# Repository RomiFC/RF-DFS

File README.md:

# :satellite: Radio Frequency Direction Finding System

The RF-DFS is a movable 3-meter dish antenna with azimuth and elevation drivers to locate the source of RF interference. This project combines the function of the DFS with the RF - Environmental Monitoring System; a similar utility that is built off of an effectively isotropic antenna. Both RF chains are connected to a Keysight N9040B Spectrum Analyzer and are controlled by a Python GUI.

**Hardware:** Automation Direct P1AM-100 PLC with 15-point discrete output module, Parker Hannifin ACR9000 Motion Controller, 2 Aries AR-04AE Servo Drives, Keysight N9040B Spectrum Analyzer, and a Windows computer.

## 🏗️ Tech Stack

```mermaid
graph BT

    subgraph Hardware
    P1AM
    win[Windows Machine]
    ACR9000
    AR-04AE
    N9040B
    end

    subgraph Firmware
    C++
    AcroBASIC
    SCPI
    end

    subgraph client[Edge Client]
    Python([Python Front End])
    end

    subgraph Back End
    Database[(PostgreSQL<br>Database)]
    Server([Python Server])
    end

    C++ -->|Serial| Python
    AcroBASIC -->|Serial| Python
    SCPI -->|GPIB/LAN| Python

    P1AM --> C++
    win --> Python
    ACR9000 & AR-04AE --> AcroBASIC
    N9040B --> SCPI
    client --> Database
    Database <--> Server
```

## 🚀 Deployment Requirements

- [NI-VISA](https://www.ni.com/en/support/downloads/drivers/download.ni-visa.html) or other suitable PyVISA backend.
- Ethernet, GPIB, serial, or other SCPI instrument connection.
  - [NI-488.2](https://www.ni.com/en/support/downloads/drivers/download.ni-488-2.html#484357) if using GPIB.

## 🛠️ Development Requirements

- All above requirements.
- [Python 3.11+](https://www.python.org/) and an understanding of the following:
  - [tkinter](https://docs.python.org/3/library/tkinter.html#module-tkinter)
  - [pySerial](https://pypi.org/project/pyserial/)
  - [PyVisa](https://pyvisa.readthedocs.io/en/latest/)
  - [matplotlib](https://matplotlib.org/)
- Suitable Python IDE (Recommended [VSCode](https://code.visualstudio.com/))
- Python packager (Recommended [PyInstaller](https://pyinstaller.org/en/stable/))
- [PlatformIO](https://platformio.org/) for updating PLC firmware.

> [!NOTE]
> Freezing tools (Such as PyInstaller) package the entire Python Interpreter and installed libraries which generates large executables and could be flagged as a virus. It is recommended to create a virtual environment and only install/package the libraries used in the program. These executables will also only work on the OS that built them (A Windows deployment must be built on a Windows computer).

### Packages

```bash
pip install pyserial
```

```bash
pip install pyvisa
```

```bash
pip install matplotlib
```

```bash
pip install numpy
```

```bash
pip install apscheduler
```

```bash
pip install ttkthemes
```

```bash
pip install tkcalendar
```

```bash
pip install tktimepicker
```

## :mailbox: Authors

- [Remy Nguyen](https://github.com/RomiFC)
- [Hina Suzuki](https://github.com/hina18201716)

<picture>
  <source media="(prefers-color-scheme: dark)" srcset="https://public.nrao.edu/wp-content/uploads/2023/02/logoGroupWhite.png">
  <source media="(prefers-color-scheme: light)" srcset="https://public.nrao.edu/wp-content/uploads/2023/02/logoGroupColor.png">
  
</picture>

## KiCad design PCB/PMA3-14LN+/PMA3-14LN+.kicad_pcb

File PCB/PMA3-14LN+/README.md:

# Changelog

## Revision B - 10/24/2023

### Added

- More PTH vias around and directly under RF components.
- Another layer of via picketing around transmission line.
- Silkscreen revision indicator.
- Dimensioning to assembly drawing.

### Changed

- Removed Hammond 1554B compatibility due to difficulties in assembly and weatherproofing SMA connectors. Overall board is smaller at 35mm x 35mm.
- SMA Connectors replaced with Mueller BU-1420761881 which have an upper frequency of 26.5 GHz and better impedance matching at the landing.
- GCPW dimensions from w = 0.415mm, s = 0.6mm, to w = 0.37mm, s = 0.2mm and added 0.375mm taper from SMA clearance to GCPW clearance.

### Fixed

- C9 footprint now correctly matches schematic (0402 --> 1206).
- Moved SMA footprints closer to board edge to reduce filing prior to assembly.

## Revision A - 4/12/2023

### First revision 🎉🎉🎉

- Board is built to 4-layer OSHPark specifications
- This amplifier showed slightly lower gain than expected, rolling off quicker with frequency. This is likely due to the SMA connector landings which had a known impedance mismatch, resulting in a steep rolloff somewhere between 12 and 18 GHz.

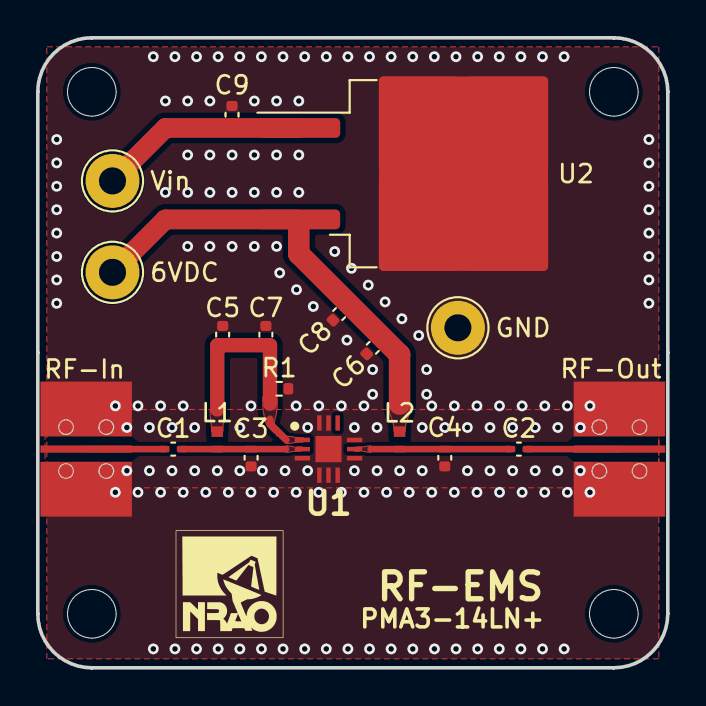
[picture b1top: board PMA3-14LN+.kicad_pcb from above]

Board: 4 copper layers, 35.0 x 35.0 mm, 20 parts (0 on the bottom side), 8 nets.

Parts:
6VDC: 6VDC; TestPoint_Loop_D2.54mm_Drill1.5mm_Beaded
 : FabDrawing-4Layer-Metric-Compact-OSH
C1, C2: 0.01 uF; C_0402_1005Metric
C3: 0.2 pF; C_0402_1005Metric
C4: 0.1 pF; C_0402_1005Metric
C5, C6: 100 pF; C_0402_1005Metric
C7: 0.1 uF; C_0402_1005Metric
C8: 0.1 uf; C_0402_1005Metric
C9: 0.33 uF; C_0402_1005Metric
GND: GND; TestPoint_Loop_D2.54mm_Drill1.5mm_Beaded
L1, L2: 900 nH; L_0402_1005Metric
R1: 510 Ω; R_0402_1005Metric
RF-In: Conn_Coaxial; Mueller BU-1420761881-RevB
RF-Out: Conn_Coaxial; Mueller BU-1420761881-RevB
U1: PMA3-14LN+; QFN51P300X300X89-13N
U2: L7806; TO-263-2
Vin: Vin; TestPoint_Loop_D2.54mm_Drill1.5mm_Beaded

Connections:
6VDC: 6VDC.1, C6.1, C8.1, L2.1, U2.3 (OUT)
GND: C3.1, C4.1, C5.1, C6.2, C7.1, C8.2, C9.2, GND.1, R1.2, RF-In.2 (Ext), RF-Out.2 (Ext), U1.3 (NC_1), U1.4 (NC_2), U1.5 (NC_3), U1.6 (NC_4), U1.7 (NC_5), U1.9 (NC_6), U1.11 (NC_8), U1.12 (NC_9), U1.13 (GND), U2.2 (GND)
unnamed: C5.2, C7.2, L1.1, R1.1, U1.1 (CURRENT_MIRROR)
unnamed: C1.2, C3.2, L1.2, U1.2 (RF-IN)
unnamed: C2.1, C4.2, L2.2, U1.8 (RF-OUT_&_VDD)
unnamed: C1.1, RF-In.1 (In)
unnamed: C2.2, RF-Out.1 (In)
Vin: C9.1, U2.1 (IN), Vin.1

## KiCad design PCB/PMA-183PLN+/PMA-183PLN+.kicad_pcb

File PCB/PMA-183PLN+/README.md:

# Changelog

## Revision B - 7/5/2023

### Added

- More PTH vias around and directly under RF components.
- Another layer of via picketing around transmission line.
- Silkscreen revision indicator.
- Dimensioning to assembly drawing.

### Changed

- Removed Hammond 1554B compatibility due to difficulties in assembly and weatherproofing SMA connectors.
- GCPW dimensions from w = 0.41mm, s = 0.2mm, to w = 0.37mm, s = 0.2mm and added 0.375mm taper from SMA clearance to GCPW clearance.

### Fixed

- C9 footprint now correctly matches schematic (0402 --> 1206).
- Moved SMA footprints closer to board edge to reduce filing prior to assembly.

## Revision A - 6/12/2023

### First revision 🎉🎉🎉

- Board is built to 4-layer OSHPark specifications
- Testing shows amplifier oscillates strongly at ~18.5 GHz. This occurs both when the amplifier is biased through the regulator or directly from a DC power supply. SMA landings were also copied from test coupons so that can likely be ruled out. This is possibly due to the lack of PTH vias directly under the IC or the tuning/spacing of picketing around the transmission line.

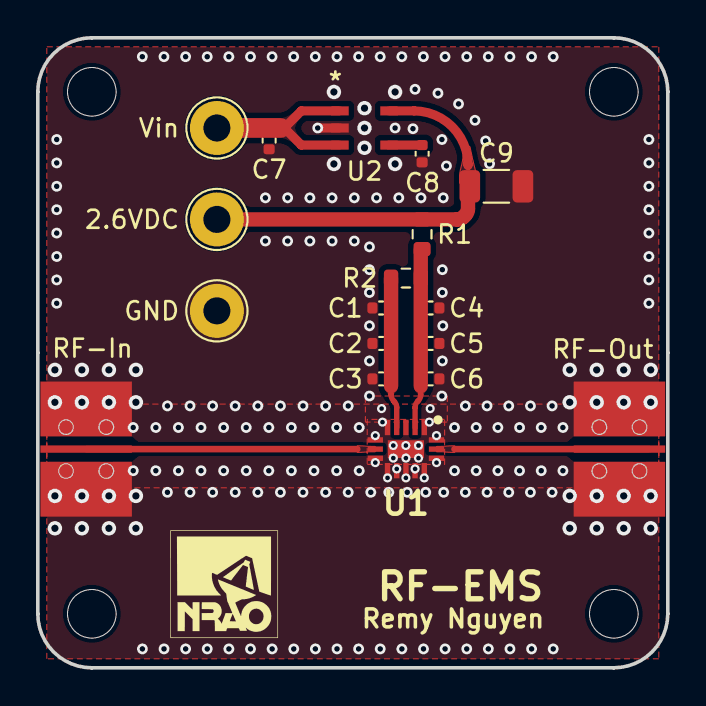
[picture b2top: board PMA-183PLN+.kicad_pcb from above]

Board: 4 copper layers, 35.0 x 35.0 mm, 20 parts (0 on the bottom side), 8 nets.

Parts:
2.6VDC: 2.6VDC; TestPoint_Loop_D2.54mm_Drill1.5mm_Beaded
 : FabDrawing-4Layer-Metric-Compact-OSH
 #2: LOGO; GCPW_osh3_90mm_user
C1, C4, C7: 0.33 uF; C_0402_1005Metric
C2, C5: 1000 pF; C_0402_1005Metric
C3, C6: 100 pF; C_0402_1005Metric
C8: 470 pF; C_0402_1005Metric
C9: 2.2 uF; C_1206_3216Metric
GND: GND; TestPoint_Loop_D2.54mm_Drill1.5mm_Beaded
R1: 10 Ω; R_0603_1608Metric
R2: 180 Ω; R_0603_1608Metric
RF-In: Conn_Coaxial; Mueller BU-1420761881
RF-Out: Conn_Coaxial; Mueller BU-1420761881
U1: PMA-183PLN+; QFN51P250X350X85-17N
U2: MIC5219-2.6YM5-TR; SOT-23-5_M5_MCH
Vin: Vin; TestPoint_Loop_D2.54mm_Drill1.5mm_Beaded

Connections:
2.6VDC: 2.6VDC.1, C9.1, R1.2, U2.5 (OUT)
GND: C1.1, C2.1, C3.1, C4.2, C5.2, C6.2, C7.2, C8.2, C9.2, GND.1, RF-In.2 (Ext), RF-Out.2 (Ext), U1.1 (NC_1), U1.3 (NC_2), U1.5 (NC_3), U1.6 (GND_1), U1.8 (GND_2), U1.9 (NC_4), U1.10 (NC_5), U1.11 (NC_6), U1.12 (NC_7), U1.13 (NC_8), U1.14 (GND_3), U1.16 (GND_4), U1.17 (EP), U2.2 (GND)
unnamed: RF-In.1 (In), U1.7 (RF-IN)
unnamed: RF-Out.1 (In), U1.15 (RF-OUT)
unnamed: C4.1, C5.1, C6.1, R1.1, R2.2, U1.2 (VDD)
unnamed: C1.2, C2.2, C3.2, R2.1, U1.4 (VE)
unnamed: C8.1, U2.4 (BYP)
Vin: C7.1, U2.1 (IN), U2.3 (EN), Vin.1

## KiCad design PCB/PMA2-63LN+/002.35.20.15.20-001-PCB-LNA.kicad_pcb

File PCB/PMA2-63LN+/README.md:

# Changelog

## Revision C - 2/23/2024

### Added

- SMA connectors dimensioned.

### Changed

- Drawing sheets changed from A4 to Letter size.
- New stackup table format.

### Fixed

- SMA launch pad widened with ground plane cutout to improve Z-matching.
- Mounting holes now correctly part of GND net.

## Revision B - 1/23/2024

### Added

- GCPW cross-section to assembly drawing.
- Board characteristics to assembly drawing.
- Board dimensioning to assembly drawing.
- Test points for DC power as an alternative to SMA.
- Test points for Iadj control.
- More PTH vias around and directly under RF components.
- Layer indicator to top left of assembly drawing.

### Changed

- Stackup changed from 2-layer, 30 mil RO4350b to 4-layer OSHPark specifications.
- Board compacted in attempt to reduce oscillations from quarter-wave resonance.
- Connector references changed from J- to more descriptive names.

### Fixed

- Removed back mask from linear regulator pads to improve thermal conductance.
- Iadj resistor to ground replaced with voltage divider for control from +5VDC to GND.

## Revision A - 7/6/2023

### First revision 🎉🎉🎉

- Board is built on 30-mil Rogers RO4350b with 2 layers. Contains two LNAs with their own linear regulators and a 1 dB attenuator between them to improve return loss.
- Testing shows amplifier instability/oscillations at ~10.8 GHz with both PMA2-63LN+ and PMA2-123LN+. This was caused by shunt capacitance introduced from the relatively large SMA landing pads and Molex center conductor.
- 30-mil substrate proved to be thin and more prone to breakage/flexing, especially when torquing SMA connectors.

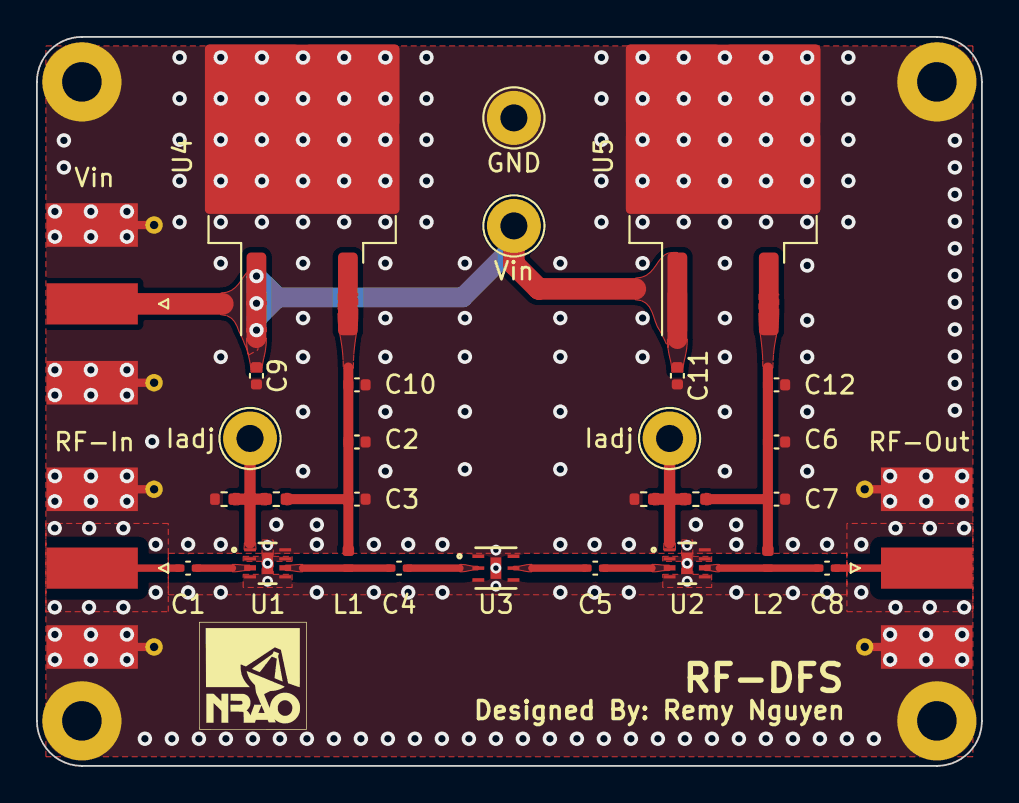
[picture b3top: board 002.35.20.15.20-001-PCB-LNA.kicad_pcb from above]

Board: 4 copper layers, 52.5 x 40.5 mm, 30 parts (0 on the bottom side), 14 nets.

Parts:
C1, C4, C5, C8: 150pF; C_0402_1005Metric
C2, C6: 1uF; C_0402_1005Metric
C3, C7: 100pF; C_0402_1005Metric
C9, C11: 0.33uF; C_0402_1005Metric
C10, C12: 0.1uF; C_0402_1005Metric
GND: GND; TestPoint_Loop_D2.54mm_Drill1.5mm_Beaded
Iadj: TestPoint; TestPoint_Loop_D2.54mm_Drill1.5mm_Beaded
Iadj#2: TestPoint; TestPoint_Loop_D2.54mm_Drill1.5mm_Beaded
L1, L2: 56nH; L_0402_1005Metric
R1, R2, R3, R4: 100k; R_0402_1005Metric
RF-In: Conn_Coaxial; SMA_Molex_73251-1153_EdgeMount_Horizontal
RF-Out: Conn_Coaxial; SMA_Molex_73251-1153_EdgeMount_Horizontal
U1, U2: PMA2-63LN+; SON8_PMA2_MNC
U3: YAT-1A+; MC1630_MNC
U4, U5: L7805; TO-263-2
Vin: Vin; TestPoint_Loop_D2.54mm_Drill1.5mm_Beaded
Vin#2: Conn_Coaxial; SMA_Molex_73251-1153_EdgeMount_Horizontal

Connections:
/LNA Biasing1/LNA-IN: C1.1, RF-In.1 (In)
/LNA Biasing1/LNA-OUT: C4.2, U3.2 (RF-IN)
/LNA Biasing2/LNA-IN: C5.1, U3.5 (RF-OUT)
/LNA Biasing2/LNA-OUT: C8.2, RF-Out.1 (In)
GND: C2.2, C3.2, C6.2, C7.2, C9.2, C10.2, C11.2, C12.2, GND.1, R1.1, R2.1, RF-In.2 (Ext), RF-Out.2 (Ext), U1.2 (GND), U1.4 (GND), U1.5 (GND), U1.7 (GND), U1.8 (GND), U1.9 (EPAD), U2.2 (GND), U2.4 (GND), U2.5 (GND), U2.7 (GND), U2.8 (GND), U2.9 (EPAD), U3.1 (GND), U3.3 (GND), U3.4 (GND), U3.6 (GND), U3.7 (GND), U4.2 (GND), U5.2 (GND), Vin#2.2 (Ext)
unnamed: Iadj#2.1, R1.2, R3.1, U1.1 (LADJ)
unnamed: C1.2, U1.3 (RF-IN)
unnamed: C4.1, L1.2, U1.6 (RF-OUT)
unnamed: Iadj.1, R2.2, R4.1, U2.1 (LADJ)
unnamed: C5.2, U2.3 (RF-IN)
unnamed: C8.1, L2.2, U2.6 (RF-OUT)
Vdd1: C2.1, C3.1, C10.1, L1.1, R3.2, U4.3 (OUT)
Vdd2: C6.1, C7.1, C12.1, L2.1, R4.2, U5.3 (OUT)
Vin: C9.1, C11.1, U4.1 (IN), U5.1 (IN), Vin.1, Vin#2.1 (In)

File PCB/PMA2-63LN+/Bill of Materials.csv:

"#","Reference","Qty","Value","Footprint","DNP"
"1","C1, C4, C5, C8","4","150pF","Capacitor_SMD:C_0402_1005Metric",""
"2","C2, C6","2","1uF","Capacitor_SMD:C_0402_1005Metric",""
"3","C3, C7","2","100pF","Capacitor_SMD:C_0402_1005Metric",""
"4","C9, C11","2","0.33uF","Capacitor_SMD:C_0402_1005Metric",""
"5","C10, C12","2","0.1uF","Capacitor_SMD:C_0402_1005Metric",""
"6","J1, J2, J3","3","Conn_Coaxial","Connector_Coaxial:SMA_Molex_73251-1153_EdgeMount_Horizontal",""
"7","L1, L2","2","56nH","Inductor_SMD:L_0402_1005Metric",""
"8","R1, R2","2","100k","Resistor_SMD:R_0402_1005Metric",""
"9","U1, U2","2","PMA2-63LN+","Imports:SON8_PMA2_MNC",""
"10","U3","1","YAT-1A+","Imports:MC1630_MNC",""
"11","U4, U5","2","L7805","Package_TO_SOT_SMD:TO-263-2",""

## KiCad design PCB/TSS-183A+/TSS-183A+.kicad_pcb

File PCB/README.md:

# Board Files

Any footprints, symbols, and models, not included with KiCad 7.0/8.0 should be added the libraries in [_dependencies](./_dependencies). Ensure that all projects are in their own directory and that each project is linked to the following library paths:

### Footprints

```pcbnew
${KIPRJMOD}/../_dependencies/footprints
```

### Symbols

```pcbnew
${KIPRJMOD}/../_dependencies/symbols/rf-dfs.kicad_sym
```

### 3D Models

Footprints should be linked to imported 3D models using the following path:

```pcbnew
${KIPRJMOD}/../_dependencies/3dmodels/<FILE_NAME>.STEP
```

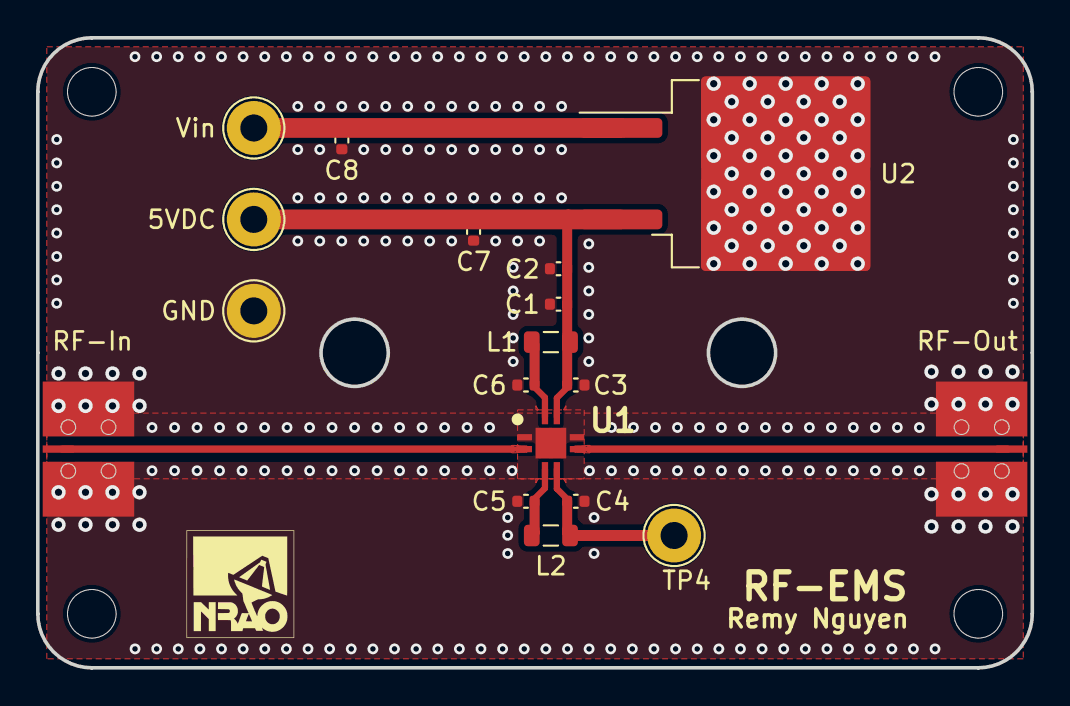
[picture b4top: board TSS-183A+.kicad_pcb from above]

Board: 4 copper layers, 55.3 x 35.0 mm, 20 parts (0 on the bottom side), 8 nets.

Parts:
5VDC: 5VDC; TestPoint_Loop_D2.54mm_Drill1.5mm_Beaded
 : LOGO; GCPW_osh2_90mm_user
 #2: FabDrawing-4Layer-Metric-Compact-OSH
C1: 5.6 pF; C_0402_1005Metric
C2: 18 pF; C_0402_1005Metric
C3, C4, C5: 1 nF; C_0402_1005Metric
C6, C7: 0.1 uF; C_0402_1005Metric
C8: 0.33 uF; C_0402_1005Metric
GND: GND; TestPoint_Loop_D2.54mm_Drill1.5mm_Beaded
L1, L2: 3.3 nH; L_0805_2012Metric
RF-In: Conn_Coaxial; Mueller BU-1420761881
RF-Out: Conn_Coaxial; Mueller BU-1420761881
TP4: Vg; TestPoint_Loop_D2.54mm_Drill1.5mm_Beaded
U1: TSS-183A+; QFN66P300X300X89-9N
U2: L7805; TO-263-2
Vin: Vin; TestPoint_Loop_D2.54mm_Drill1.5mm_Beaded

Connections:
5VDC: 5VDC.1, C1.1, C2.1, C3.1, C7.1, L1.1, U1.7 (VDD2), U2.3 (OUT)
GND: C1.2, C2.2, C3.2, C4.1, C5.2, C6.1, C7.2, C8.2, GND.1, RF-In.2 (Ext), RF-Out.2 (Ext), U1.1 (NC_1), U1.6 (NC_2), U1.9 (EP), U2.2 (GND)
unnamed: RF-In.1 (In), U1.2 (RF-IN)
unnamed: RF-Out.1 (In), U1.5 (RF-OUT)
unnamed: C6.2, L1.2, U1.8 (VDD1)
unnamed: C5.1, L2.1, U1.3 (VG1)
unnamed: C4.2, L2.2, TP4.1, U1.4 (VG2)
Vin: C8.1, U2.1 (IN), Vin.1

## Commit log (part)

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2024-07-05 Updated RF block diagram
2024-07-09 Fixed PMA2-63LN+ changelog dates
2024-08-06 PLC code added with basic functionality
    - Successfully receives and parses strings from serial into opcodes.
    - Needs additional functionality/opcodes for configuration and error messaging
2024-08-07 Moved opcodes to opcodes.h and added doxygen comments (PLC)
2024-08-07 Changed opcode syntax for sleep operations (PLC)
2024-08-07 Added more opcode functionality to plc
2024-08-09 Fixed bug where scpiApplyConfig called ttk::spinbox get() twice
2024-08-09 Limited GUI root window size to initial value
2024-08-09 Multiple changes in functions.py
    - Methods serialInterface and scpiInterface changed to controlTab and configTab in prep for full system integration of serial/scpi/plc functionality
    - Placeholder labelFrame added to tab 1 in place of spectrum analyzer window
    - Widgets in method controlTab sorted based on column
    - Widgets in tab 1 (controlTab) now scale based on window size
2024-08-12 Added placeholder widgets to analyzer frame in gui
2024-08-13 GUI object vi changed to Vi for naming consistency
2024-08-16 Updated readme.md"
2024-08-19 Updated NRAO logo for dark and light mode
2024-08-20 Multiple changes to GUI
    - Moved class FrontEnd variables/constants to __init__
    - Moved Vi object of class VisaControl to __init__
    - Added timestamp.py which prepends print call with a timestamp
    * @file opcodes.py
    * @author Remy Nguyen (rnguyen@nrao.edu)
    * @brief Header file that contains opcode declarations for the P1AM-100 PLC.
2024-08-21 Moved class FrontEnd from functions.py to main.py to prevent circular import when multithreading
2024-08-21 Renamed file functions.py to frontendio.py
2024-08-22 Embedded matplotlib plot to gui which tracks analyzer trace
2024-08-22 New methods FrontEnd.initAnalyzerPlotValues() and FrontEnd.setAnalyzerPlotValues()
2024-08-23 Added amplifier labels to report figure
2024-08-26 Changes to gui-dev spectrum analyzer plot
    - initAnalyzerDisplay() ==> loopAnalyzerDisplay() which should not
    return for the duration of thread t1's life
    - toggleAnalyzerDisplay() now only sets analyzerKillFlag and does not
    interact with threading at all
2024-08-26 gui-dev additions to FrontEnd spectrum analyzer widgets
    - Spectrum analyzer widgets now contain self parameter
    - Entry widget validation on keypress tested but not fully implemented
    - New method setAnalyzerValue(self, **kwargs) to control
    synchronization between analyzer config and widget values
2024-08-29 Entry widgets validate on keypress, console scrolls to bottom when new message is inserted
2024-08-29 Additions to gui-dev analyzer widgets
    - New function clearAndSetEntry(widget, arg) deletes all values in widget and
    replaces it with arg
    - Spectrum analyzer plot ttk::Entry widgets bound to
    FrontEnd.setAnalyzerValue() on <Return>
    - Function isNumber now tests for scientific notation and decimals
    - FrontEnd.setAnalyzerValue() tested successfully with centerfreq
2024-08-29 FrontEnd.resetWidgetValues() changed to FrontEnd.resetConfigWidgets()
2024-08-30 Updated .gitignore
2024-08-30 Deleted cached kicad files
2024-08-30 Updated main.py and frontendio.py docstrings
2024-08-30 Changes to gui analyzer display and multithreaded visa communications
    - setAnalyzerValues not instantiates a list of dictionaries based on
    kwargs, then iterates through the list to issue visa commands (Reduces
    lines of code in each if statement)
    - New threading events AllowAnalyzer and isAnalyzerActive to allow main
    thread and t1 to communicate. main thread will wait for t1's display
    loop to end when setAnalyzerValue is called and set AllowAnalyzer to
2024-09-03 Fixed fatal bug where calls to setAnalyzerValue would interrupt :READ:SAN?
    - setAnalyzerValue moved to analyzerThreadHandler which creates an
    independent thread. This thread acquires a lock so that only one
    function can issue VISA commands at a time.
    - loopAnalyzerDisplay sets and acquires lock between sleep time
    - Issue persists where an out of range VISA command creates a fatal
    error (such as stop frequency > 52 GHz).
2024-09-05 Minor changes to gui
    - Plot axes have title and labels
    - Moved instantiation of `DFS_Window` after `console` so that logging
    functions in __init__ are placed in the console window
    - Moved resetAnalyzerState to frontendio.py
    - Changed print calls in frontendio.py to logging
2024-09-06 Included pcb libraries in repository under '_dependencies' with projects linked to them using relative paths
2024-09-11 Added ttk:combobox functionality to setAnalyzerValue
    - Changed func clearAndSetEntry to clearAndSetWidget which works for
    combobox and with strings as an argument
    - List constants changed to type tuple
2024-09-11 Disabled axis autoscaling
2024-09-12 Spectrum Analyzer plot now automatically sets limits
    - Moved initAnalyzerPlotLimits functionality to setAnalyzerPlotLimits
    - Removed method initAnalyzerPlotLimits
    - setAnalyzerPlotLimits gets parameters from widgets instead of visa
    queries to reduce thread locking and redundant visa queries.
    - setAnalyzerValue initializes arg:None for keys which may influence
    plot limits, then calls setAnalyzerPlotLimits in case a visa write
2024-09-12 Added auto/manual radiobutton functionality
    - Bug persists where radiobuttons do not update entries
2024-09-13 Fixed bug where exception is not logged in loopAnalyzerDisplay
2024-09-13 Added visa queries for :SYST:ERR
2024-09-13 clearAndSetWidget now converts argument to engineering notation using module 'decimal'
2024-09-17 Theme additions
    - Moved motor port selection to config tab, added plc port selection to config
    tab.
    - Added ttk theme to root window
    - Changed combobox highlight color to match regular colors to prevent
    blue highlight whenever an option is selected (does not work in
    readonly state)
2024-09-19 Moved spectrum analyzer plot to its own class, object Vi of VisaControl() is now passed to both objects of FrontEnd and SpecAn
2024-09-20 Report: changed rfblock to phase 3 diagram, added phase 2 diagram
2024-10-10 loopAnalyzerDisplay now checks Operation Status before beginning sweep
    - New methods getEventRegister, getOperationRegister, and
    getCalCondRegister in class VisaControl.
    - Added single sweep button.
2024-10-10 Removed control/config tabs in favor of menubar organization. resetConfigwidgets() is now deprecated
2024-10-10 changed polar plot colors
2024-10-11 Started moving azimuth and elevation entries to class AziElePlot
    - Still needs work to save motor port in variable instead of getting
    from widget motorSelectBox (It only exists when 'Configure...' menu is
    open"
2024-10-11 Added debug console
2024-10-14 Added logging level TERMINAL
    - Added docstring to setAnalyzerValue and fixed combobox not setting
    default arg to None
    - Moved tkVars to class SpecAn from class FrontEnd
2024-10-14 Implemented trace and log saving
2024-10-15 New control and status widgets
    - Changed root geometry manager from pack to grid
    - New method FrontEnd.setStatus for buttons being used as status
    indicators
2024-10-15 Changed scope of some widgets in FrontEnd.openConfig() and made text argument of FrontEnd.setStatus() optional
2024-10-17 Added class PLCIO in frontendio.py:
    - Contains methods for Serial communications (For PLC but can be reused
    for general serial communications). Contains it's own thread handler
    and lock as opposed to VisaIO, where threading and locking is handled
    outside of the class.
    - OpCode sending and receiving tested successfully.
2024-10-17 Added PLC operation buttons to front end (kind of, needs work)
2024-10-22 Changed some lock.acquire()/release() calls to 'with lock:...'
2024-10-22 Fixed bug where serial query delay was not working as intended and added longer delay to P1_INIT/P1_DISABLE commands
2024-10-22 Changed plcOperationStateMachine case statements from shorthand string to opcodes, removed some visa error handling that resulted in extraneous printing
2024-10-23 Added loggingsetup.py
    - Moved logging configuration to loggingsetup.py with new level VERBOSE
    - Moved FrontEnd.openConfig.onConnect() functionality to
    FrontEnd.initDevice()
    - Changed some logging.debug calls to logging.verbose
2024-10-23 Housekeeping
2024-10-24 Updated PMA3-14LN+ Changelog
2024-10-24 Fixed board clearance in PMA3 -14LN+
2024-10-28 Class PLCIO renamed to SerialIO (will likely be used for motor as well)
2024-10-28 Added 'save image' functionality
2024-10-30 Added save trace as csv functionality
2024-10-30 PLC now keeps track of status (output conditions) and can be queried for status
2024-10-30 Front end now updates PLC state
    - New thread statusMonitorPLC which constantly monitors the attribute
    SerialIO.status for changes.
    - SerialIO.write now has the argument getStatus to determine whether or
    not to send a opcodes.QUERY_STATUS message 1.2 seconds after the
    original message. This delay is required but may be fixable in the
    PLC code.
2024-11-01 PLC no longer returns query opcode
2024-11-01 Added disconnect buttons to resources in config menu
2024-11-18 Spantype and sweep time implemented
2024-11-18 setAnalyzerValue kwargs changed to args
2024-11-19 Added y axis unit to amp tab of spec an controls
2024-12-02 Added 'open wiki' to help menu
2025-02-10 Spec_An.loopAnalyzerDisplay changed to finite state machine
    - New functions disableChildren() and enableChildren() for tkinter
    frames
    - New method Spec_An.toggleInputs() to utilize previous functions
    - Spectrum plots now enable and disable based on thread state
2025-02-10 Fixed spectrum widget sizing
2025-02-10 Added write/read/query methods to MotorIO because the preexisting methods are overly convoluted and I don't want to break things yet
2025-02-10 Added threading.RLock to MotorIO serial calls
2025-02-11 Added logging level MOTOR to write/read/query methods of class MotorIO
2025-02-11 Partially implemented az/el state machine (UNTESTED)
    - Added exception type to error logging.
    - Added drive status to status monitor thread
2025-02-12 Motor encoder counts successfully parsed from program, still needs implementation
2025-02-13 Fixed some window resizing bugs
2025-02-13 Updated defaultconfig.py with (uncalibrated) encoder values
2025-02-13 AziEle state machine now plots on axes
2025-02-13 Changed AziElePlot.sendMoveCommand to simple Motor.write call
2025-02-14 Motor command angle changed to last command
2025-02-14 Fixed polar title intersecting with labels
2025-02-14 Added state machine delay constants
2025-03-20 Changed thread names for consistency
2025-04-24 Updated folder settings.json
2025-04-24 Added user guide
2025-04-30 doc: added switches to sysblock2
2025-05-01 doc: updated rf block diagram
2025-05-01 doc: rf signal chain and hig changes
2025-05-01 doc: added terminal section from wiki
2025-05-02 doc: i hate tikz
2025-05-02 doc: wiring diagram fixed jfc
2025-05-02 doc: more wiring
2025-05-05 doc: another block diagram and fixed some wiring stuff
2025-05-05 doc: shack components section and ems power wiring diagram
2025-05-06 doc: changes to sec 3, 3.1, added appendix
2025-05-06 doc: additions to sections 3, 3.1, 3.2, added another diagram to ems appendix figure
2025-05-08 doc: motor position and opcodes
2025-05-09 doc: idek a bunch of wiring diagrams ig
2025-05-09 doc: stuff
2025-05-12 doc: more stuff
2025-05-12 doc: appendices
2025-05-13 doc: drift stuff and table row colors
2025-05-15 doc: fixed sma fig perspective
2025-05-15 doc: added loto to figures
2025-05-30 doc: misc changes
2025-05-30 gui: changed spectrum analyzer list of dict syntax to actual class (class Parameter).
2025-05-30 gui: added header to saved traces
2025-06-02 gui: auto date stuff
2025-06-05 gui: added automation parameters to defaultconfig
2025-06-05 gui: automation works
2025-06-05 gui: added trace type parameter
2025-06-05 gui: cleanup and added halt movement & kill drives buttons (untested)
